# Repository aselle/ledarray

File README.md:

# ledarray
Tileable LED Array Based with RP2040 Micropython Display

## License

HW is licensed under CERN Open Hardware Licence Version 2 - Permissive
and software is licensed under MIT

## Warranty

No warranty is offered, given, or implied, but see license for details.

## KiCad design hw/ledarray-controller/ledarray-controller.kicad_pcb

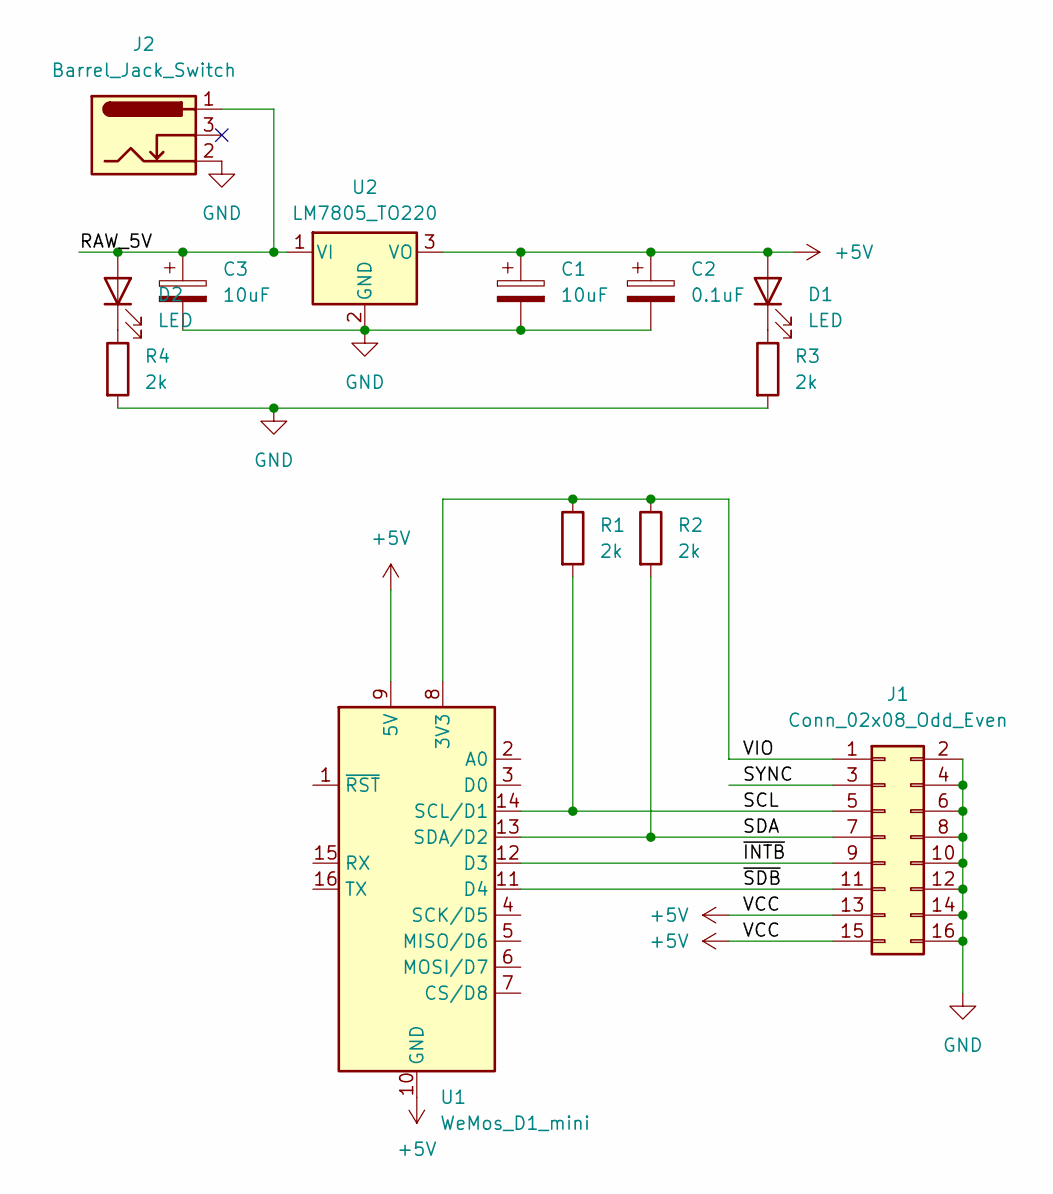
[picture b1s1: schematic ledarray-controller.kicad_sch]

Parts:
C1, C3: 10uF; CP_Radial_D8.0mm_P2.50mm
C2: 0.1uF; CP_Radial_D8.0mm_P2.50mm
D1, D2: LED; LED_D5.0mm
J1: Conn_02x08_Odd_Even; IDC-Header_2x08_P2.54mm_Vertical; LCSC C4749181
J2: Barrel_Jack_Switch; BarrelJack_GCT_DCJ200-10-A_Horizontal
R1, R2, R3, R4: 2k; R_Axial_DIN0207_L6.3mm_D2.5mm_P10.16mm_Horizontal
U1: WeMos_D1_mini; WEMOS_D1_mini_light
U2: LM7805_TO220; TO-220-3_Vertical

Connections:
+5V: C1.1, C2.1, D1.2 (A), J1.13, J1.15, U1.9 (5V), U1.10 (GND), U2.3 (VO)
/RAW_5V: C3.1, D2.2 (A), J2.1, U2.1 (VI)
/SCL: J1.5, R1.2, U1.14 (SCL/D1)
/SDA: J1.7, R2.2, U1.13 (SDA/D2)
/SYNC: J1.3
/VIO: J1.1, R1.1, R2.1, U1.8 (3V3)
/~INTB: J1.9, U1.12 (D3)
/~SDB: J1.11, U1.11 (D4)
GND: C1.2, C2.2, C3.2, J1.2, J1.4, J1.6, J1.8, J1.10, J1.12, J1.14, J1.16, J2.2, R3.2, R4.2, U2.2 (GND)
unnamed: D1.1 (K), R3.1
unnamed: D2.1 (K), R4.1

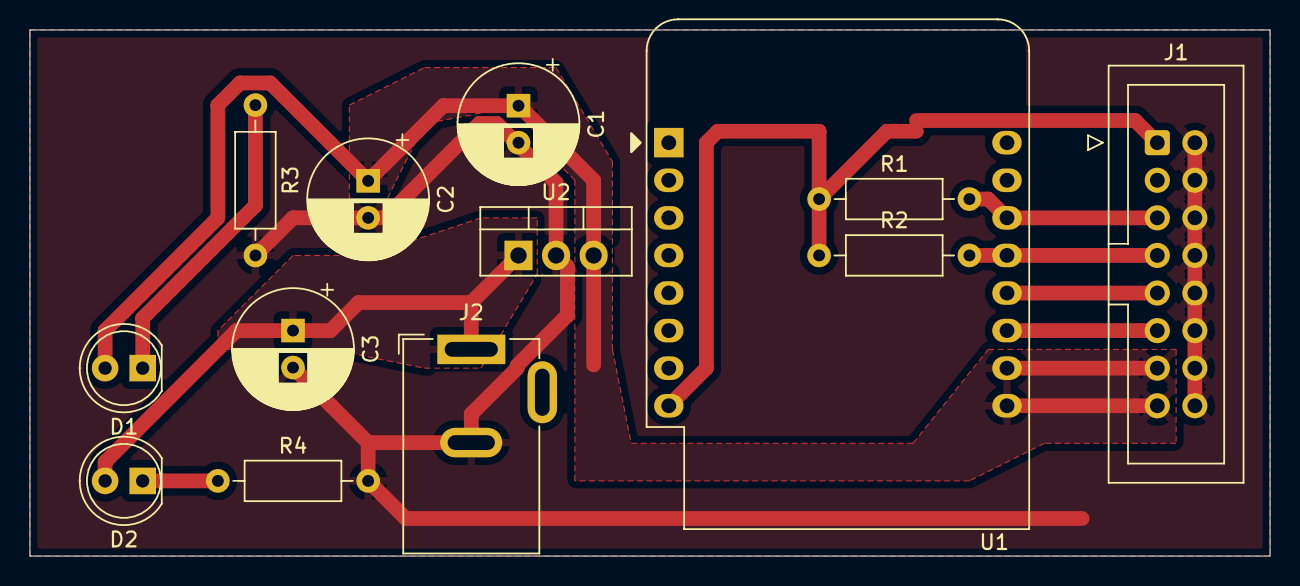
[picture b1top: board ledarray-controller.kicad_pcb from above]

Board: 2 copper layers, 83.8 x 35.6 mm, 13 parts (0 on the bottom side), 10 nets.

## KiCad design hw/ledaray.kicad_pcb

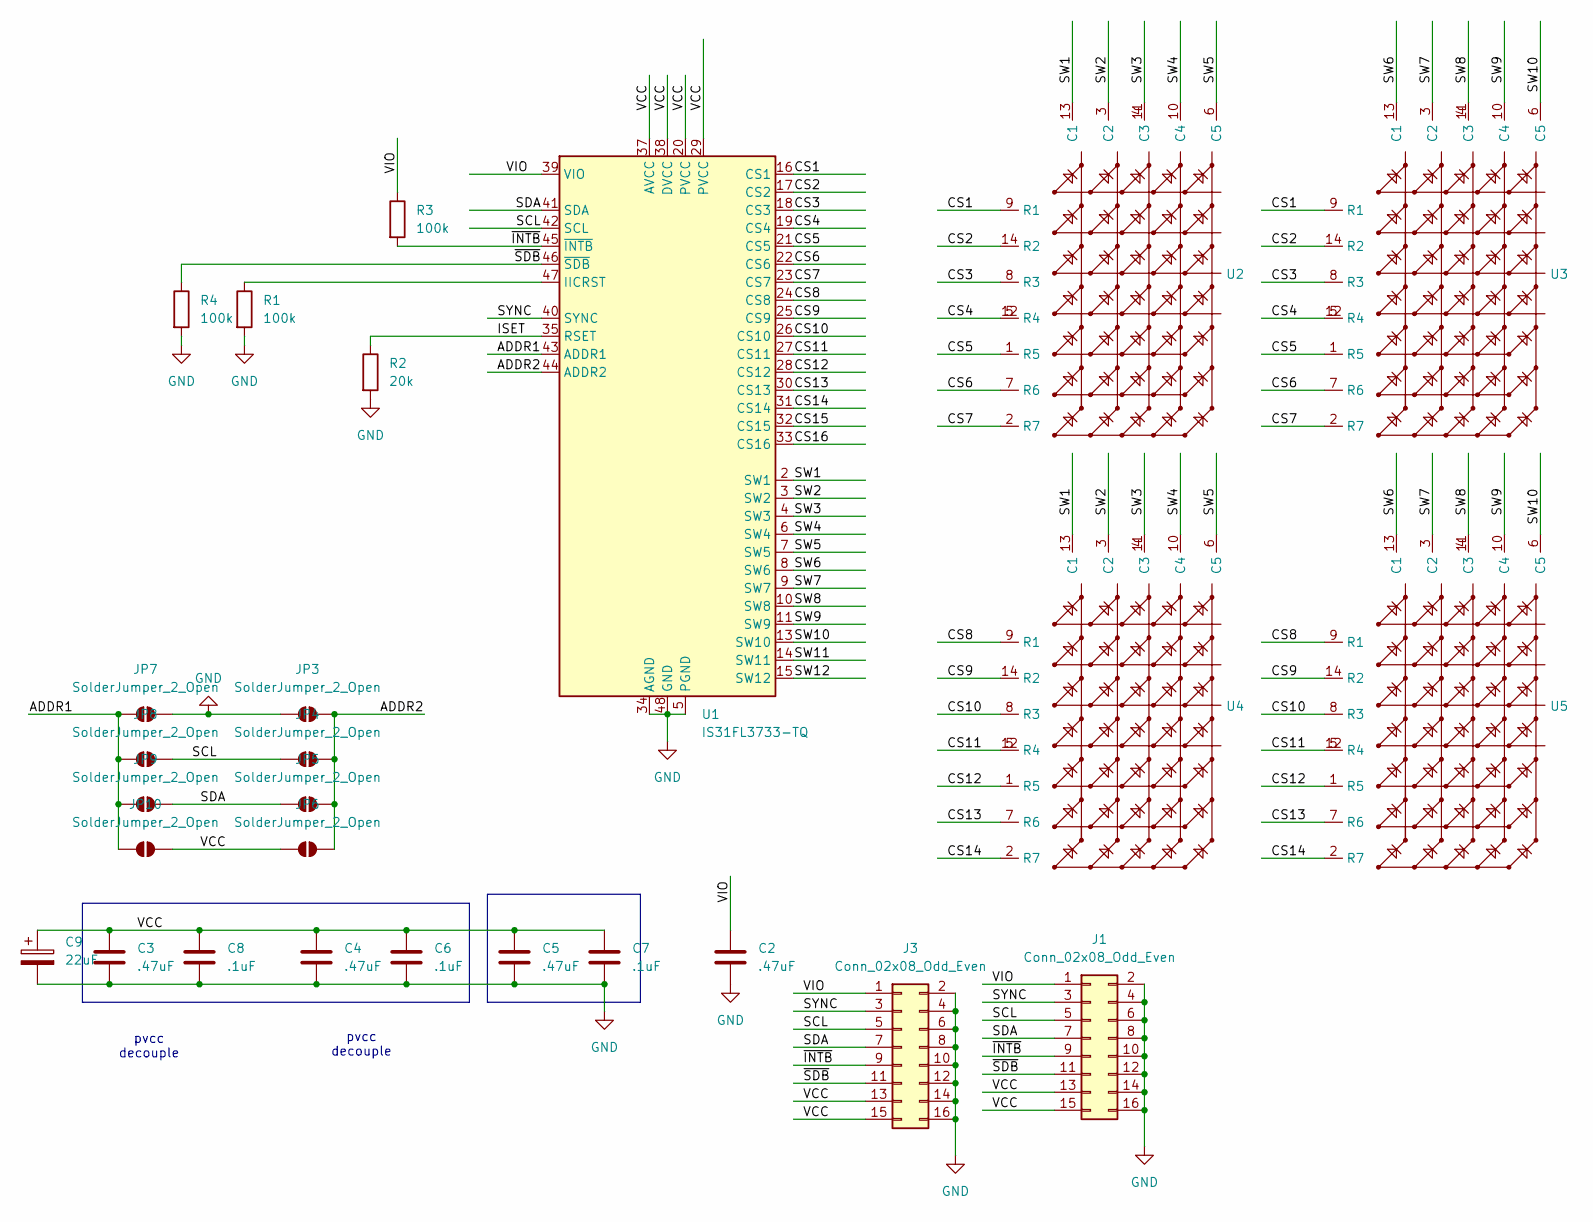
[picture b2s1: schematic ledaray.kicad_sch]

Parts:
C2, C3, C4, C5: .47uF; C_0805_2012Metric
C6, C7, C8: .1uF; C_0805_2012Metric
C9: 22uF; CP_Elec_5x5.3
J1, J3: Conn_02x08_Odd_Even; IDC-Header_2x08_P2.54mm_Vertical_SMD; LCSC C4749181
JP3, JP4, JP5, JP6, JP7, JP8, JP9, JP10: SolderJumper_2_Open; SolderJumper-2_P1.3mm_Open_TrianglePad1.0x1.5mm
R1, R3, R4: 100k; R_0805_2012Metric
R2: 20k; R_0805_2012Metric
U1: IS31FL3733-TQ; QFN-48-1EP_6x6mm_P0.4mm_EP4.2x4.2mm
U2, U3, U4, U5: LPTL21157AGBW2

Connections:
/ADDR1: JP7.2 (B), JP8.2 (B), JP9.2 (B), JP10.2 (B), U1.43 (ADDR1)
/ADDR2: JP3.2 (B), JP4.2 (B), JP5.2 (B), JP6.2 (B), U1.44 (ADDR2)
/CS1: U1.16 (CS1), U2.9 (R1), U3.9 (R1)
/CS2: U1.17 (CS2), U2.14 (R2), U3.14 (R2)
/CS3: U1.18 (CS3), U2.8 (R3), U3.8 (R3)
/CS4: U1.19 (CS4), U2.5 (R4), U2.12 (R4), U3.5 (R4), U3.12 (R4)
/CS5: U1.21 (CS5), U2.1 (R5), U3.1 (R5)
/CS6: U1.22 (CS6), U2.7 (R6), U3.7 (R6)
/CS7: U1.23 (CS7), U2.2 (R7), U3.2 (R7)
/CS8: U1.24 (CS8), U4.9 (R1), U5.9 (R1)
/CS9: U1.25 (CS9), U4.14 (R2), U5.14 (R2)
/CS10: U1.26 (CS10), U4.8 (R3), U5.8 (R3)
/CS11: U1.27 (CS11), U4.5 (R4), U4.12 (R4), U5.5 (R4), U5.12 (R4)
/CS12: U1.28 (CS12), U4.1 (R5), U5.1 (R5)
/CS13: U1.30 (CS13), U4.7 (R6), U5.7 (R6)
/CS14: U1.31 (CS14), U4.2 (R7), U5.2 (R7)
/CS15: U1.32 (CS15)
/CS16: U1.33 (CS16)
/ISET: R2.1, U1.35 (RSET)
/SCL: J1.5, J3.5, JP4.1 (A), JP8.1 (A), U1.42 (SCL)
/SDA: J1.7, J3.7, JP5.1 (A), JP9.1 (A), U1.41 (SDA)
/SW1: U1.2 (SW1), U2.13 (C1), U4.13 (C1)
/SW2: U1.3 (SW2), U2.3 (C2), U4.3 (C2)
/SW3: U1.4 (SW3), U2.4 (C3), U2.11 (C3), U4.4 (C3), U4.11 (C3)
/SW4: U1.6 (SW4), U2.10 (C4), U4.10 (C4)
/SW5: U1.7 (SW5), U2.6 (C5), U4.6 (C5)
/SW6: U1.8 (SW6), U3.13 (C1), U5.13 (C1)
/SW7: U1.9 (SW7), U3.3 (C2), U5.3 (C2)
/SW8: U1.10 (SW8), U3.4 (C3), U3.11 (C3), U5.4 (C3), U5.11 (C3)
/SW9: U1.11 (SW9), U3.10 (C4), U5.10 (C4)
/SW10: U1.13 (SW10), U3.6 (C5), U5.6 (C5)
/SW11: U1.14 (SW11)
/SW12: U1.15 (SW12)
/SYNC: J1.3, J3.3, U1.40 (SYNC)
/VCC: C3.1, C4.1, C5.1, C6.1, C7.1, C8.1, C9.1, J1.13, J1.15, J3.13, J3.15, JP6.1 (A), JP10.1 (A), U1.20 (PVCC), U1.29 (PVCC), U1.37 (AVCC), U1.38 (DVCC)
/VIO: C2.1, J1.1, J3.1, R3.1, U1.39 (VIO)
/~INTB: J1.9, J3.9, R3.2, U1.45 (~INTB)
/~SDB: J1.11, J3.11, R4.1, U1.46 (~SDB)
GND: C2.2, C3.2, C4.2, C5.2, C6.2, C7.2, C8.2, C9.2, J1.2, J1.4, J1.6, J1.8, J1.10, J1.12, J1.14, J1.16, J3.2, J3.4, J3.6, J3.8, J3.10, J3.12, J3.14, J3.16, JP3.1 (A), JP7.1 (A), R1.2, R2.2, R4.2, U1.5 (PGND), U1.12 (PGND), U1.34 (AGND), U1.48 (GND), U1.49 (GND)
unnamed: R1.1, U1.47 (IICRST)

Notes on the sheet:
pvcc decouple

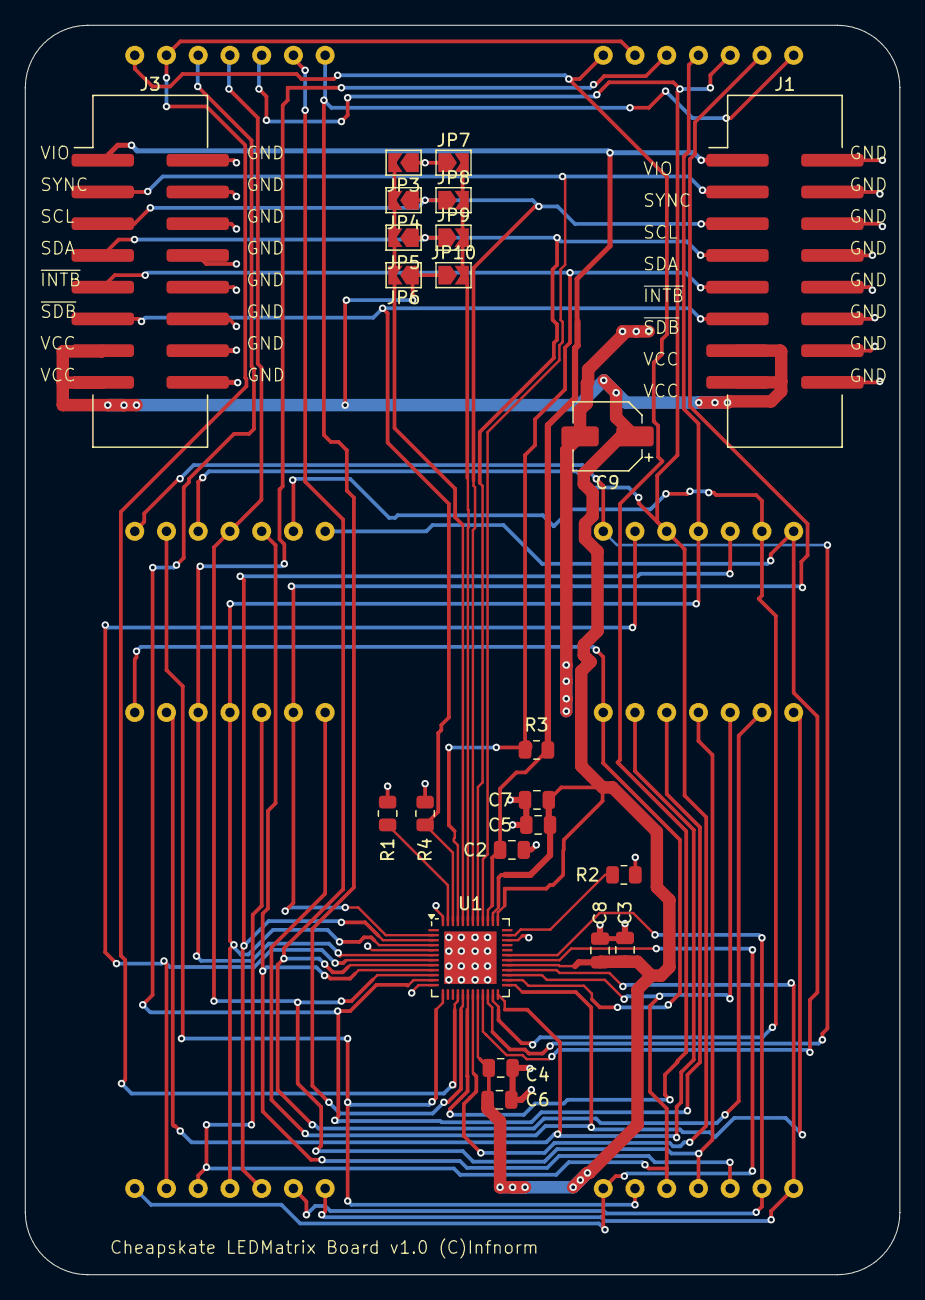
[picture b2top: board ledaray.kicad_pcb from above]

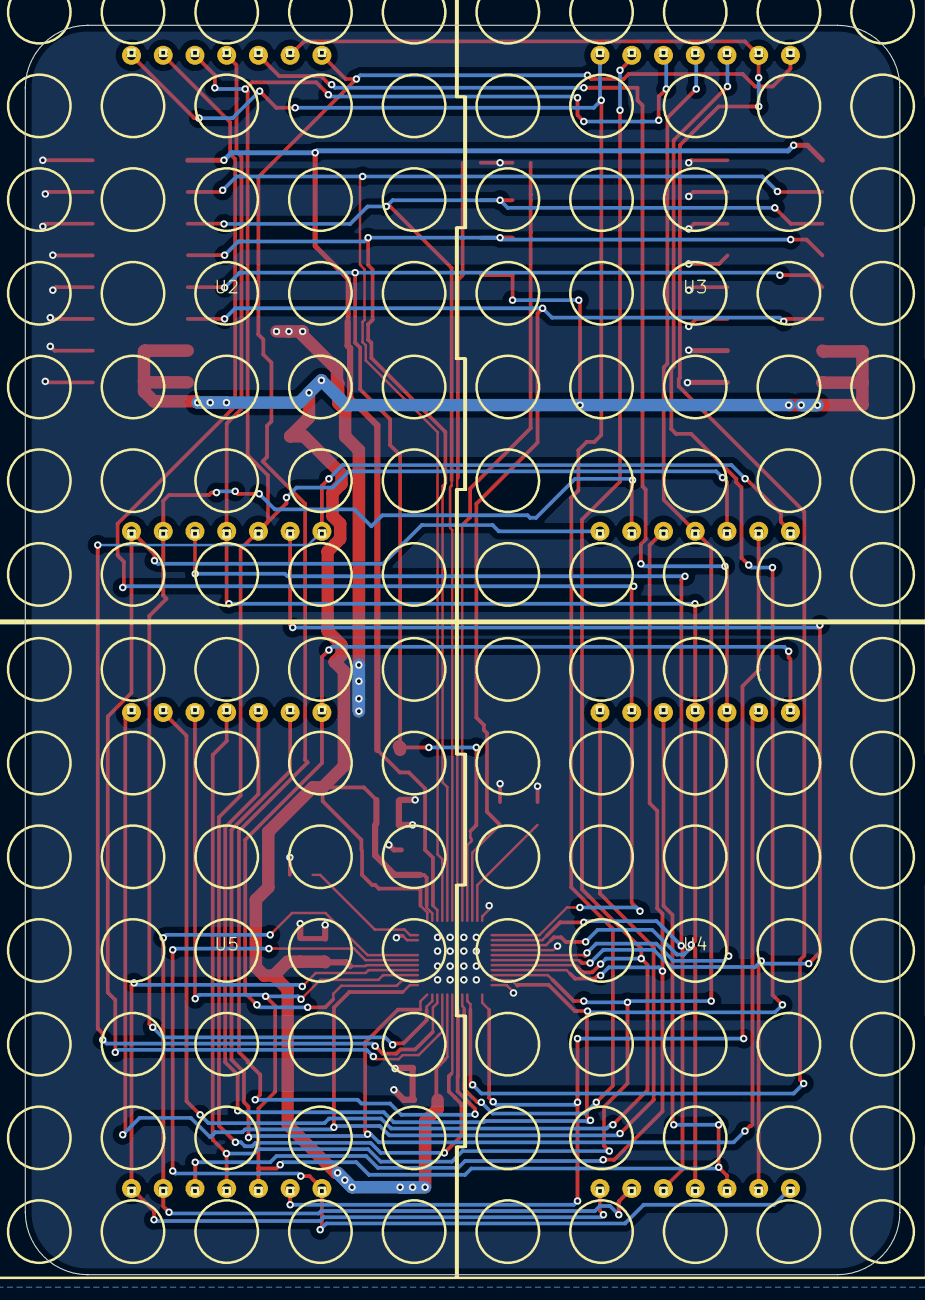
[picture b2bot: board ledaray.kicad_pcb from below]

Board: 2 copper layers, 70.0 x 100.0 mm, 27 parts (4 on the bottom side), 36 nets.

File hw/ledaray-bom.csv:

Id;Designator;Footprint;Quantity;Designation;Supplier and ref
1;C3,C2,C4,C5;C_0805_2012Metric;4;.47uF;C16780 
2;C6,C8,C7;C_0805_2012Metric;3;.1uF;C49678 
3;R2;R_0805_2012Metric;1;20k;C4328 
4;U1;QFN-48-1EP_6x6mm_P0.4mm_EP4.2x4.2mm;1;IS31FL3733-TQ;C506251 
5;R3,R1,R4;R_0805_2012Metric;3;100k;C96346 
6;C9;CP_Elec_5x5.3;1;22uF;C4747978 
7;J1,J3;IDC-Header_2x08_P2.54mm_Vertical_SMD;2;Conn_02x08_Odd_Even;C2685064 
8;U2,U5,U3,U4;LPTL21157AGBW2;4;~;

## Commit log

2025-06-09 Clarify license for hardware
